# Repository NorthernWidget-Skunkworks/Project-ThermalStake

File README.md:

# Project-ThermalStake
Rugged state with embedded thermistors to measure groundwater--surface-water exchange

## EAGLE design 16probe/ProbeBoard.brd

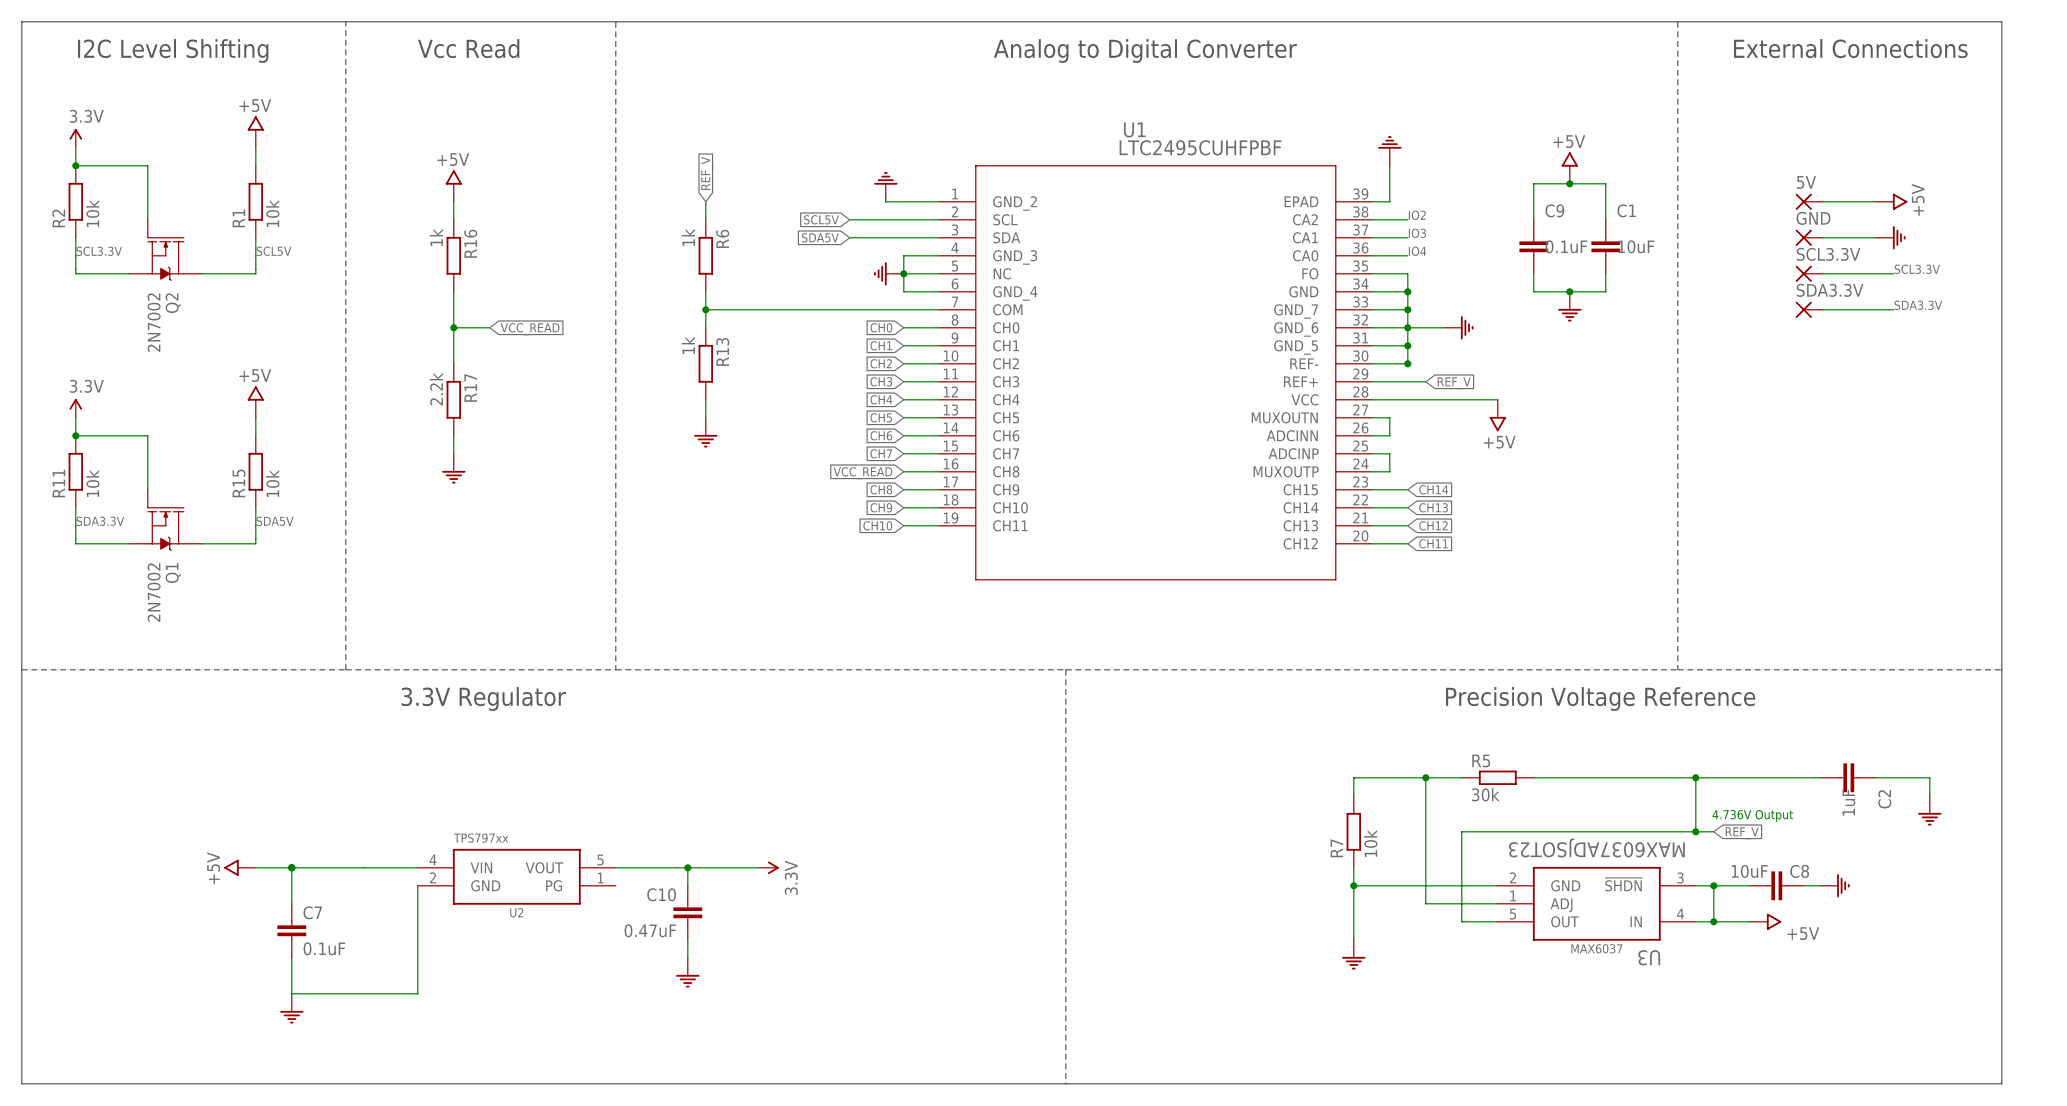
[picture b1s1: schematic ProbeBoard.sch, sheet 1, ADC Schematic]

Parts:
5V: 1,6/0,9
C1, C8: 10uF; C0603; MANUFACTURER_PART_NUMBER C1608X7S0J106M080AC; DIGIKEY_PART_NUMBER 445-9104-6-ND
C2: 1uF; C0603; MANUFACTURER_PART_NUMBER CL10B105KA8NNNC; DIGIKEY_PART_NUMBER 1276-1184-6-ND
C7, C9: 0.1uF; C0603; MANUFACTURER_PART_NUMBER 0603ZC104KAT2A; DIGIKEY_PART_NUMBER 478-7939-2-ND
C10: 0.47uF; C0603; MANUFACTURER_PART_NUMBER 0603ZC474KAT2A; DIGIKEY_PART_NUMBER 478-10367-1-ND
GND: 1,6/0,9
Q1, Q2: 2N7002; SOT323
R1, R2, R7, R11, R15: 10k; R0603; MANUFACTURER_PART_NUMBER ERJ-3GEYJ103V; DIGIKEY_PART_NUMBER P10KGTR-ND
R5: 30k; R0603; MANUFACTURER_PART_NUMBER ERJ-3GEYJ303V; DIGIKEY_PART_NUMBER P30KGDKR-ND
R6, R13, R16: 1k; R0603; MANUFACTURER_PART_NUMBER ERA-3AEB102V; DIGIKEY_PART_NUMBER P1.0KDBDKR-ND
R17: 2.2k; R0603; MANUFACTURER_PART_NUMBER ERA-3AEB222V; DIGIKEY_PART_NUMBER P2.2KDBTR-ND
SCL3.3V: 1,6/0,9
SDA3.3V: 1,6/0,9
U1: LTC2495CUHFPBF; QFN-38_UHF; DIGIKEY_PART_NUMBER LTC2495IUHF#PBF-ND
U2: TPS79733; DCK_R-PDSO-G5
U3: MAX6037ADJSOT23; SOT23-5; DIGIKEY_PART_NUMBER MAX6037AAUK33+TCT-ND

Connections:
3.3V: C10.2, Q1.1 (G), Q2.1 (G), R2.2, R11.2, U2.5 (VOUT)
+5V: 5V.1, C1.1, C7.1, C8.2, C9.1, R1.2, R15.2, R16.1, U1.28 (VCC), U2.4 (VIN), U3.3 (!SHDN), U3.4 (IN); also elsewhere on the board
CH0: U1.8 (CH0); also elsewhere on the board
CH1: U1.9 (CH1); also elsewhere on the board
CH2: U1.10 (CH2); also elsewhere on the board
CH3: U1.11 (CH3); also elsewhere on the board
CH4: U1.12 (CH4); also elsewhere on the board
CH5: U1.13 (CH5); also elsewhere on the board
CH6: U1.14 (CH6); also elsewhere on the board
CH7: U1.15 (CH7); also elsewhere on the board
CH8: U1.17 (CH9); also elsewhere on the board
CH9: U1.18 (CH10); also elsewhere on the board
CH10: U1.19 (CH11); also elsewhere on the board
CH11: U1.20 (CH12); also elsewhere on the board
CH12: U1.21 (CH13); also elsewhere on the board
CH13: U1.22 (CH14); also elsewhere on the board
CH14: U1.23 (CH15); also elsewhere on the board
COM: C1.2, C2.1, C7.2, C8.1, C9.2, C10.1, GND.1, R7.1, R13.2, R17.2, U1.1 (GND_2), U1.4 (GND_3), U1.5 (NC), U1.6 (GND_4), U1.30 (REF-), U1.31 (GND_5), U1.32 (GND_6), U1.33 (GND_7), U1.34 (GND), U1.35 (FO), U1.39 (EPAD), U2.2 (GND), U3.2 (GND); also elsewhere on the board
IO2: U1.38 (CA2); also elsewhere on the board
IO3: U1.37 (CA1); also elsewhere on the board
IO4: U1.36 (CA0); also elsewhere on the board
unnamed: U1.26 (ADCINN), U1.27 (MUXOUTN)
unnamed: U1.24 (MUXOUTP), U1.25 (ADCINP)
unnamed: R6.2, R13.1, U1.7 (COM)
unnamed: R5.1, R7.2, U3.1 (ADJ)
REF_V: C2.2, R5.2, R6.1, U1.29 (REF+), U3.5 (OUT)
SCL3.3V: Q2.2 (S), R2.1, SCL3.3V.1
SCL5V: Q2.3 (D), R1.1, U1.2 (SCL); also elsewhere on the board
SDA3.3V: Q1.2 (S), R11.1, SDA3.3V.1
SDA5V: Q1.3 (D), R15.1, U1.3 (SDA); also elsewhere on the board
VCC_READ: R16.2, R17.1, U1.16 (CH8)

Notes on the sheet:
4.736V Output
Analog to Digital Converter
External Connections
Vcc Read
I2C Level Shifting
3.3V Regulator
Precision Voltage Reference

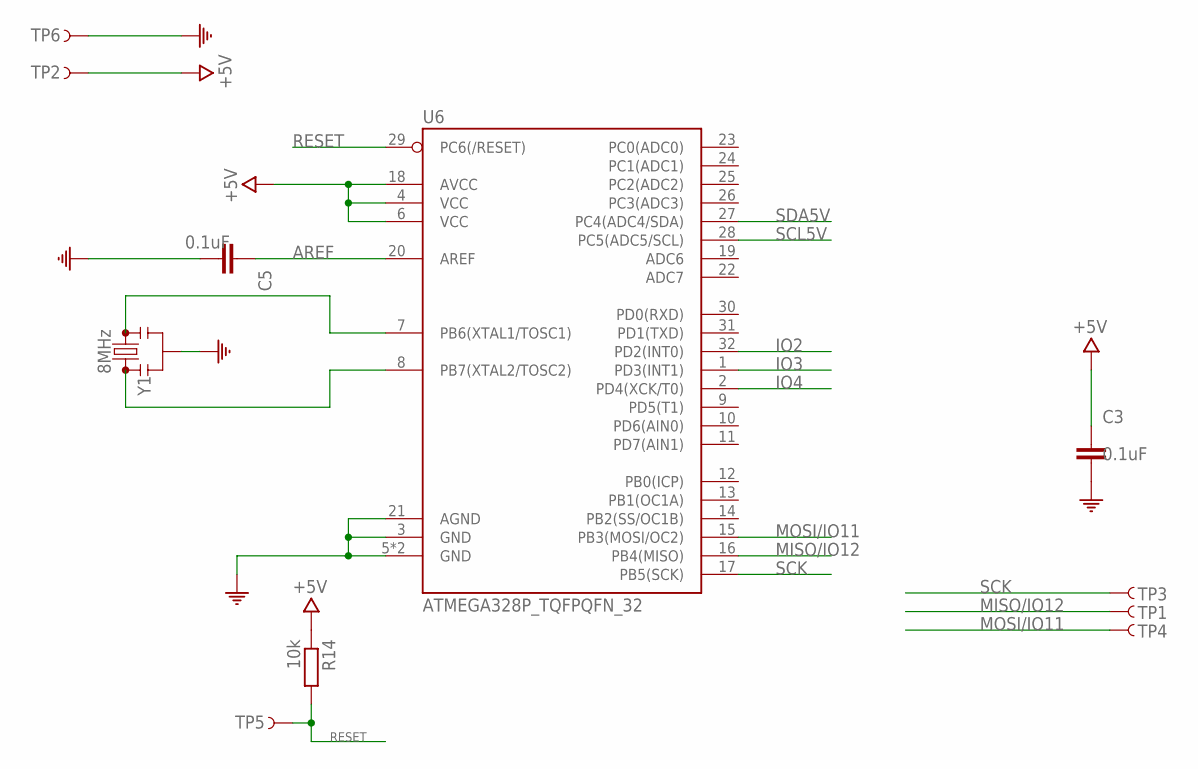
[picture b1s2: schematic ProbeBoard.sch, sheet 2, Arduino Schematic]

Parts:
C3, C5: 0.1uF; C0603; MANUFACTURER_PART_NUMBER 0603ZC104KAT2A; DIGIKEY_PART_NUMBER 478-7939-2-ND
R14: 10k; R0603; MANUFACTURER_PART_NUMBER ERJ-3GEYJ103V; DIGIKEY_PART_NUMBER P10KGTR-ND
TP1, TP2, TP3, TP4, TP5, TP6: TEST-POINT3; PAD.03X.03
U6: ATMEGA328P_TQFPQFN_32; QFN32
Y1: 8MHz; RESONATOR-SMD-3.2X1.3

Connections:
+5V: C3.1, R14.1, TP2.P$1, U6.4 (VCC), U6.6 (VCC), U6.18 (AVCC); also elsewhere on the board
AREF: C5.1, U6.20 (AREF)
COM: C3.2, C5.2, TP6.P$1, U6.3 (GND), U6.5 (GND), U6.21 (AGND), U6.EP (GND), Y1.2; also elsewhere on the board
IO2: U6.32 (PD2(INT0)); also elsewhere on the board
IO3: U6.1 (PD3(INT1)); also elsewhere on the board
IO4: U6.2 (PD4(XCK/T0)); also elsewhere on the board
MISO/IO12: TP1.P$1, U6.16 (PB4(MISO))
MOSI/IO11: TP4.P$1, U6.15 (PB3(MOSI/OC2))
unnamed: U6.7 (PB6(XTAL1/TOSC1)), Y1.3
unnamed: U6.8 (PB7(XTAL2/TOSC2)), Y1.1
RESET: R14.2, TP5.P$1, U6.29 (PC6(/RESET))
SCK: TP3.P$1, U6.17 (PB5(SCK))
SCL5V: U6.28 (PC5(ADC5/SCL)); also elsewhere on the board
SDA5V: U6.27 (PC4(ADC4/SDA)); also elsewhere on the board

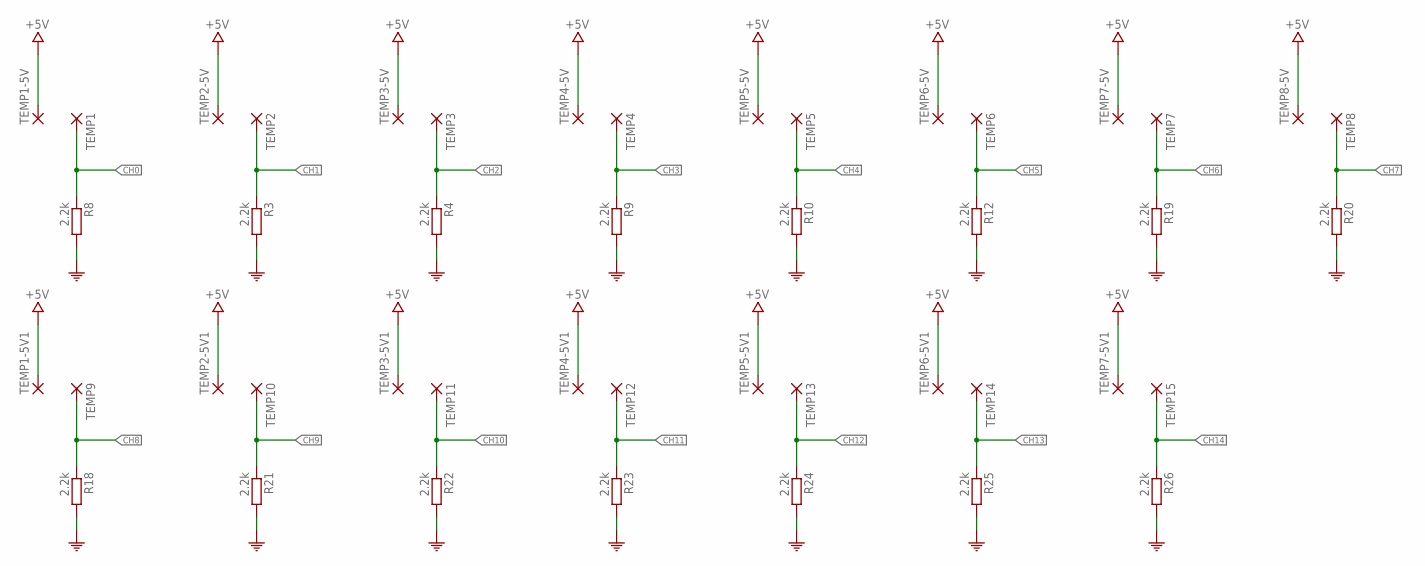
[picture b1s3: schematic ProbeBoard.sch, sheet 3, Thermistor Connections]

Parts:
R3, R4, R8, R9, R10, R12, R18, R19, R20, R21, R22, R23, R24, R25, R26: 2.2k; R0603; MANUFACTURER_PART_NUMBER ERA-3AEB222V; DIGIKEY_PART_NUMBER P2.2KDBTR-ND
TEMP1, TEMP1-5V, TEMP1-5V1, TEMP2, TEMP2-5V, TEMP2-5V1, TEMP3, TEMP3-5V, TEMP3-5V1, TEMP4, TEMP4-5V, TEMP4-5V1, TEMP5, TEMP5-5V, TEMP5-5V1, TEMP6, TEMP6-5V, TEMP6-5V1, TEMP7, TEMP7-5V, TEMP7-5V1, TEMP8, TEMP8-5V, TEMP9, TEMP10, TEMP11, TEMP12, TEMP13, TEMP14, TEMP15: 1,6/0,9

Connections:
+5V: TEMP1-5V.1, TEMP1-5V1.1, TEMP2-5V.1, TEMP2-5V1.1, TEMP3-5V.1, TEMP3-5V1.1, TEMP4-5V.1, TEMP4-5V1.1, TEMP5-5V.1, TEMP5-5V1.1, TEMP6-5V.1, TEMP6-5V1.1, TEMP7-5V.1, TEMP7-5V1.1, TEMP8-5V.1; also elsewhere on the board
CH0: R8.1, TEMP1.1; also elsewhere on the board
CH1: R3.1, TEMP2.1; also elsewhere on the board
CH2: R4.1, TEMP3.1; also elsewhere on the board
CH3: R9.1, TEMP4.1; also elsewhere on the board
CH4: R10.1, TEMP5.1; also elsewhere on the board
CH5: R12.1, TEMP6.1; also elsewhere on the board
CH6: R19.1, TEMP7.1; also elsewhere on the board
CH7: R20.1, TEMP8.1; also elsewhere on the board
CH8: R18.1, TEMP9.1; also elsewhere on the board
CH9: R21.1, TEMP10.1; also elsewhere on the board
CH10: R22.1, TEMP11.1; also elsewhere on the board
CH11: R23.1, TEMP12.1; also elsewhere on the board
CH12: R24.1, TEMP13.1; also elsewhere on the board
CH13: R25.1, TEMP14.1; also elsewhere on the board
CH14: R26.1, TEMP15.1; also elsewhere on the board
COM: R3.2, R4.2, R8.2, R9.2, R10.2, R12.2, R18.2, R19.2, R20.2, R21.2, R22.2, R23.2, R24.2, R25.2, R26.2; also elsewhere on the board

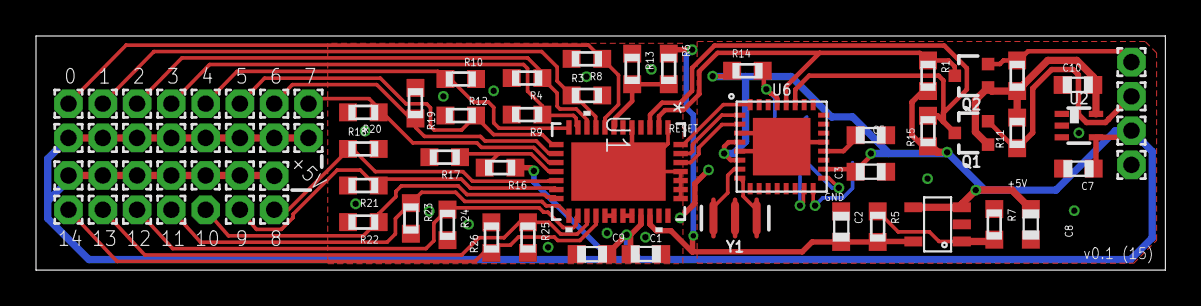
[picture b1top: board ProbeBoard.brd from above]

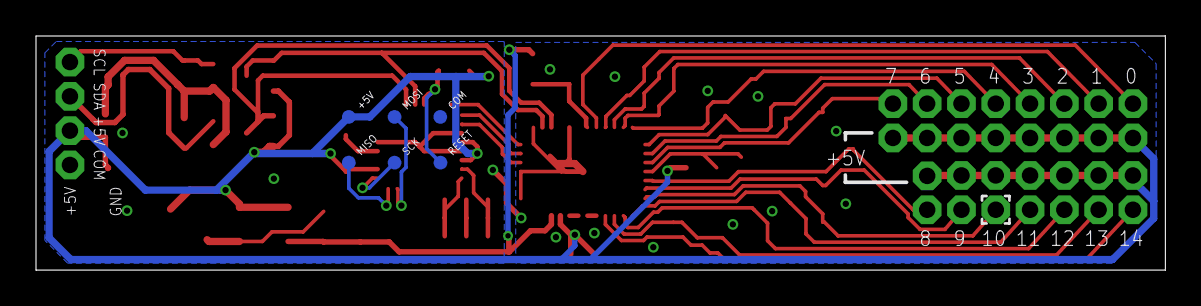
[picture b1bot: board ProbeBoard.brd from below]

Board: 2 copper layers, 62.7 x 13.0 mm, 81 parts (7 on the bottom side), 38 nets.

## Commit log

2019-02-06 Hardware license
2019-02-06 Control board by Ryan Doxsey
2019-03-19 add revised board, old reference design
2019-03-20 Minor layout updates to 8probe
    Split ground plane redistributed decoupling capacitors appropriately, moved input cable connections to be in a row, fixed package on Q1 and Q2, corrected ground pad on ATMEGA. Silk screen still needs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
2019-03-21 No spaces, no version
2019-03-26 small silkscreen tweaks, add revision number
2019-03-26 create development branch
2019-03-26 begin 16 probe layout
2019-03-28 tweak version numbers
2019-03-28 signal traces for 16 probe board
2019-04-02 probe pad placement, silkscreen
2019-04-02 small tweak to upper ground plane
2019-04-02 trim ground plane near 5V point
2019-04-03 Updates to 8probe layout, 8probe v0.1 to fab
    Minor updates and cleanup to 8probe layout, generated gerbers for 8probe v0.1 sent to fab
2019-04-04 switch out passives and crystal
2019-04-04 replace voltage reference IC
2019-04-04 shift SDA path

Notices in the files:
parts and their libraries:
SparkFun-Passives: Licensing: Creative Commons ShareAlike 4.0 International - https://creativecommons.org/licenses/by-sa/4.0
SparkFun: Licensing: CC v3.0 Share-Alike You are welcome to use this library for commercial purposes.
